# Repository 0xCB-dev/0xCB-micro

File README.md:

# 0xcb-micro
## 1% - 65% keyboard controller with RGB underglow and a backlight driver

Licence | OSHWA
:-------------------------:|:-------------------------:
 | 

#### Flashing

* `qmk clone`
* `cd qmk_firmware`
* `export LTO=Y`
* To go to bootloader hold the ESC key (row0 col0 / the key on the PCB) while plugging in (or short RST from the ISP header to GND).
* `make 0xcb/micro:via:flash`

### Assembly:

You can use the [humanpnp](https://files.0xcb.dev/0xCB-micro/humanpnp.html) to easily place components.

### PCB:
KiCad 6 stable

[Schematic](https://github.com/0xCB-dev/0xcb-micro/blob/main/rev1.0/micro.pdf)

Top | Bottom
:-------------------------:|:-------------------------:
  |  

#### BOM:
| References          | Value       | Quantity |Part Nb.          |
|---------------------|-------------|----------|------------------|
| C2, C3, C4, C5, C10 | 100n        | 5        |C478888           |
| C6, C9              | 1u          | 2        |C29936            |
| C7, C8              | 22p         | 2        |C85969            |
| C1                  | 10u         | 1        |C85713            |
| R5, R6, R8          | 10k         | 3        |C98220            |
| R1, R2              | 5.1k        | 2        |C23186            |
| R3, R4              | 22          | 2        |C174301           |
| R7, R9              | 330         | 2        |C104763           |
| D1                  | 1N4148WT    | 1        |C511874           |
| D2                  | WS2812B     | 1        |C114586           |
| U2                  | ATMEGA32U4  | 1        |ATMEGA32U4RC-MU-ND|
| U1                  | USBLC6-2SC6 | 1        |C7519             |
| Y1                  | 16MHz       | 1        |C389842           |
| F1                  | 1A          | 1        |C369150           |
| FB1                 | 600R        | 1        |C74330            |
| Q1                  | FDS9926A    | 1        |C693202           |
| J1                  | USB         | 1        |C168688           |

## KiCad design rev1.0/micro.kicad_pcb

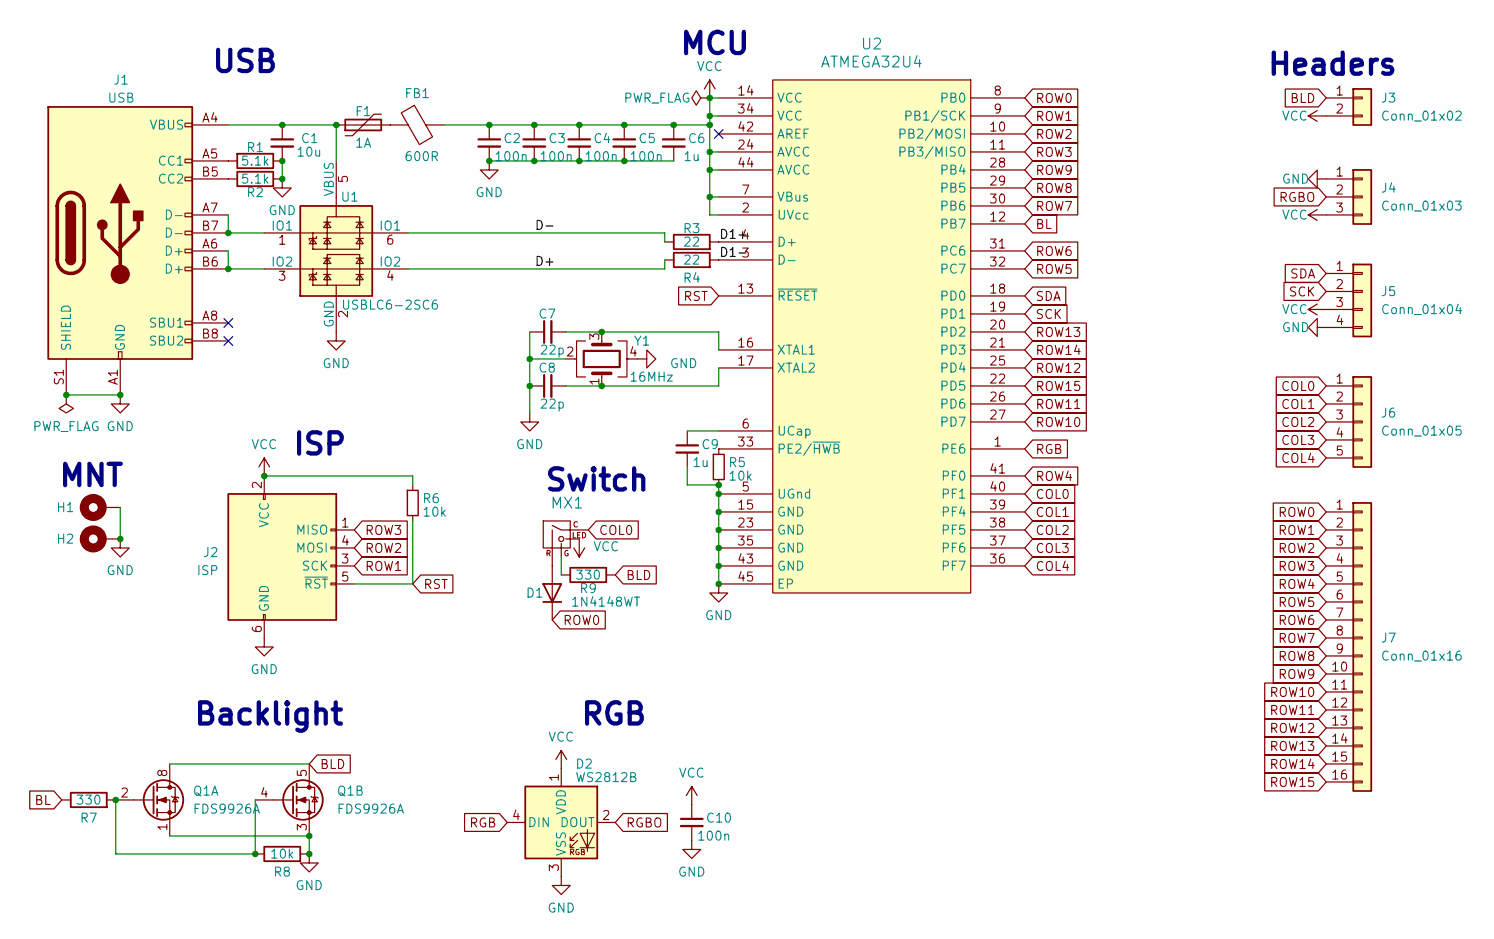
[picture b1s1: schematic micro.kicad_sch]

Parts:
C1: 10u; C_0603_1608Metric
C2, C3, C4, C5, C10: 100n; C_0603_1608Metric
C6, C9: 1u; C_0603_1608Metric
C7, C8: 22p; C_0603_1608Metric
D1: 1N4148WT; D_SOD-523
D2: WS2812B; LED_WS2812B_PLCC4_5.0x5.0mm_P3.2mm
F1: 1A; Fuse_0805_2012Metric
FB1: 600R; Ferrite_Bead_0603
H1, H2: MountingHole_Pad; MountingHole_2.2mm_M2_DIN965_Pad_TopBottom_SMOL
J1: USB; HRO-TYPE-C-31-M-13
J2: ISP; AVR_PROG_2.54_THT
J3: Conn_01x02; PinHeader_1x02_P1.27mm_Vertical
J4: Conn_01x03; PinHeader_1x03_P1.27mm_Vertical
J5: Conn_01x04; PinHeader_1x04_P1.27mm_Vertical
J6: Conn_01x05; PinHeader_1x05_P1.27mm_Vertical
J7: Conn_01x16; PinHeader_1x16_P1.27mm_Vertical
MX1: MX-LED; MXOnly-1U
Q1: FDS9926A; SOIC-8_3.9x4.9mm_P1.27mm
R1, R2: 5.1k; R_0603_1608Metric
R3, R4: 22; R_0603_1608Metric
R5, R6, R8: 10k; R_0603_1608Metric
R7, R9: 330; R_1206_3216Metric
U1: USBLC6-2SC6; SOT-23-6
U2: ATMEGA32U4; QFN-44-1EP_7x7mm_P0.5mm_EP5.2x5.2mm_ThermalVias
Y1: 16MHz; Crystal_SMD_3225-4Pin_3.2x2.5mm

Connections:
/D1+: R3.2, U2.4 (D+)
/D1-: R4.2, U2.3 (D-)
/D+: R4.1, U1.4 (IO2)
/D-: R3.1, U1.6 (IO1)
BL: R7.1, U2.12 (PB7)
BLD: J3.1, Q1.5 (D2), Q1.6 (D2), Q1.7 (D1), Q1.8 (D1), R9.2
COL0: J6.1, MX1.1 (COL), U2.40 (PF1)
COL1: J6.2, U2.39 (PF4)
COL2: J6.3, U2.38 (PF5)
COL3: J6.4, U2.37 (PF6)
COL4: J6.5, U2.36 (PF7)
GND: C1.2, C2.2, C3.2, C4.2, C5.2, C6.2, C7.1, C8.1, C9.2, C10.2, D2.3 (VSS), H1.1, H2.1, J1.A1 (GND), J1.A12 (GND), J1.B1 (GND), J1.B12 (GND), J1.S1 (SHIELD), J2.6 (GND), J4.1, J5.4, Q1.1 (S1), Q1.3 (S2), R1.1, R2.2, R5.2, R8.2, U1.2 (GND), U2.5 (UGnd), U2.15 (GND), U2.23 (GND), U2.35 (GND), U2.43 (GND), U2.45 (EP), Y1.2, Y1.4
unnamed: C1.1, F1.1, J1.A4 (VBUS), J1.A9 (VBUS), J1.B4 (VBUS), J1.B9 (VBUS), U1.5 (VBUS)
unnamed: C7.2, U2.16 (XTAL1), Y1.3
unnamed: C8.2, U2.17 (XTAL2), Y1.1
unnamed: C9.1, U2.6 (UCap)
unnamed: D1.2 (A), MX1.2 (ROW)
unnamed: F1.2, FB1.1
unnamed: J1.A5 (CC1), R1.2
unnamed: J1.A6 (D+), J1.B6 (D+), U1.3 (IO2)
unnamed: J1.A7 (D-), J1.B7 (D-), U1.1 (IO1)
unnamed: J1.B5 (CC2), R2.1
unnamed: MX1.4 (LEDGND), R9.1
unnamed: Q1.2 (G1), Q1.4 (G2), R7.2, R8.1
unnamed: R5.1, U2.33 (PE2/~HWB)
RGB: D2.4 (DIN), U2.1 (PE6)
RGBO: D2.2 (DOUT), J4.2
ROW0: D1.1 (K), J7.1, U2.8 (PB0)
ROW1: J2.3 (SCK), J7.2, U2.9 (PB1/SCK)
ROW2: J2.4 (MOSI), J7.3, U2.10 (PB2/MOSI)
ROW3: J2.1 (MISO), J7.4, U2.11 (PB3/MISO)
ROW4: J7.5, U2.41 (PF0)
ROW5: J7.6, U2.32 (PC7)
ROW6: J7.7, U2.31 (PC6)
ROW7: J7.8, U2.30 (PB6)
ROW8: J7.9, U2.29 (PB5)
ROW9: J7.10, U2.28 (PB4)
ROW10: J7.11, U2.27 (PD7)
ROW11: J7.12, U2.26 (PD6)
ROW12: J7.13, U2.25 (PD4)
ROW13: J7.14, U2.20 (PD2)
ROW14: J7.15, U2.21 (PD3)
ROW15: J7.16, U2.22 (PD5)
RST: J2.5 (~RST), R6.2, U2.13 (~RESET)
SCK: J5.2, U2.19 (PD1)
SDA: J5.1, U2.18 (PD0)
VCC: C2.1, C3.1, C4.1, C5.1, C6.1, C10.1, D2.1 (VDD), FB1.2, J2.2 (VCC), J3.2, J4.3, J5.3, MX1.3 (LED), R6.1, U2.2 (UVcc), U2.7 (VBus), U2.14 (VCC), U2.24 (AVCC), U2.34 (VCC), U2.44 (AVCC)

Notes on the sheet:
Switch
ISP
Backlight
MNT
RGB
Headers
USB
MCU

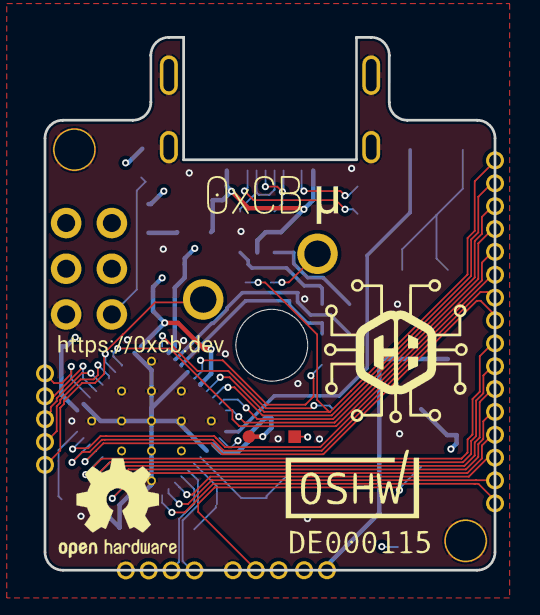
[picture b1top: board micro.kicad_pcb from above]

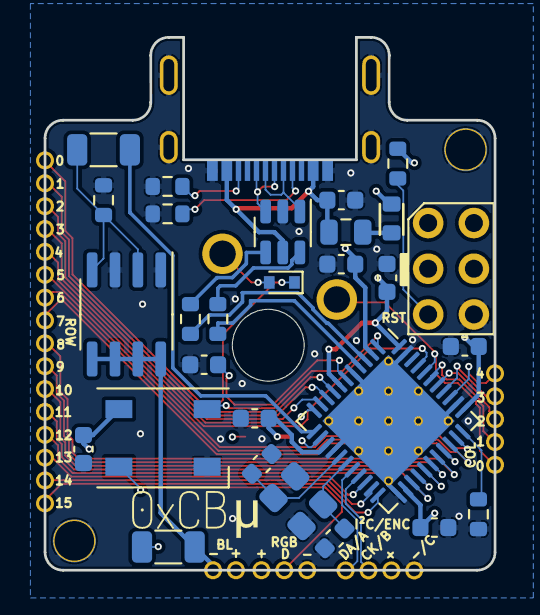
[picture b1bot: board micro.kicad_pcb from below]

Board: 4 copper layers, 25.0 x 29.6 mm, 42 parts (35 on the bottom side), 47 nets.

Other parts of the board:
0xCB: G***; svg2mod
micro: G***; svg2mod
svg2mod, svg2mod#2, svg2mod#3: G***; svg2mod

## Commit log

2022-01-08 added gitignore
2022-01-18 updated ibom link
